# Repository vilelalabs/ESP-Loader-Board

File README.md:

Project created and updated live at  [Twitch.Tv/HenriqueVilelaMusic](https://twitch.tv/henriquevilelamusic)

# ESP-Loader-Board
CAD project of a board to upload programs to the ESP 8266 family boards

## Notes
- :warning: **The Source (fonte) may be a 3.3V DC !!!**
- **J1** and **J2** may be connected through a jumper on top side of the board. 
- **J3** and **J4** may be connected through a jumper on top side of the board. 
- The **JP1** jumper is used to enable/disable the **ESP8266 "upload mode"** where, connect to the GND, is the Upload Mode.

## Tested Boards
- ESP8266-01
- ESP8266-12S
- ESP8266-12E ( add: connect GPIO15 TO ground through a 300~10k resistor).

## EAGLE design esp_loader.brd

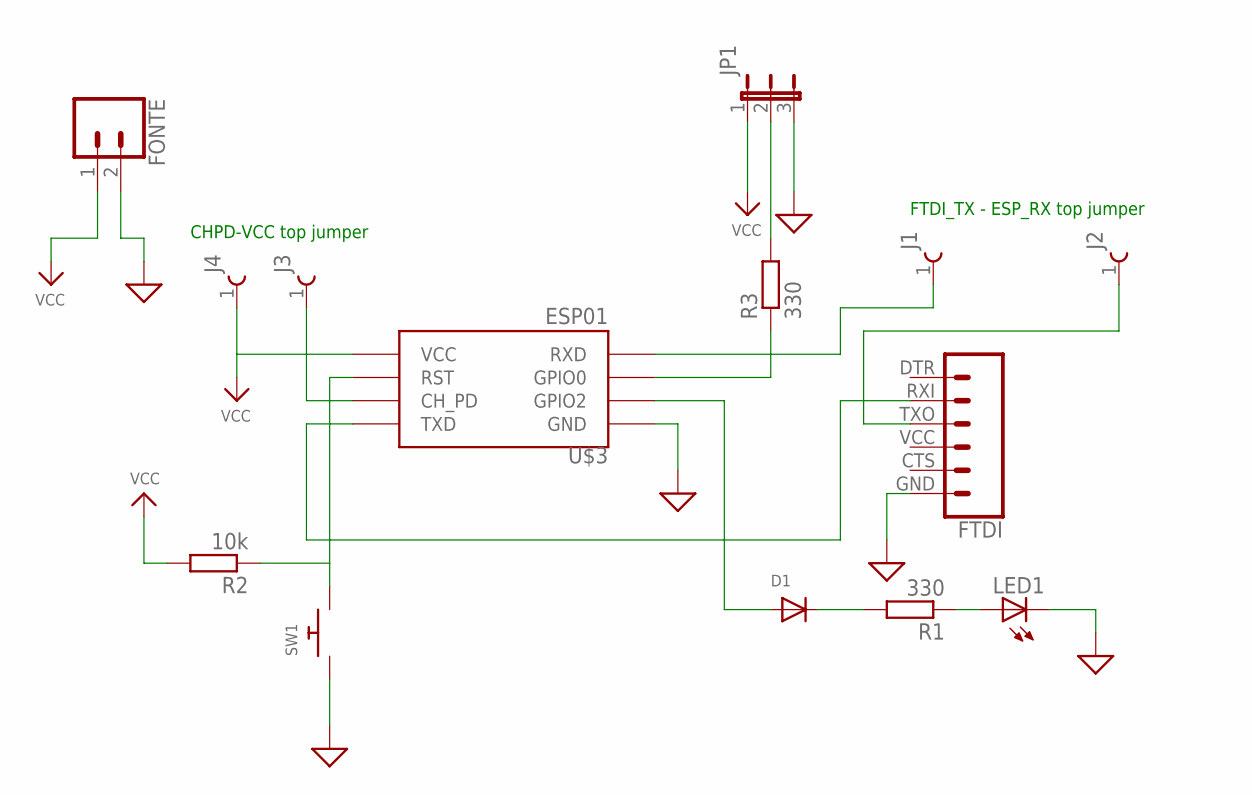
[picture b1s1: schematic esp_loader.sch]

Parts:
D1: DIODEDO-1N4148; DO-1N4148
FONTE: CONN_02POLAR; MOLEX-1X2
FTDI: 6_PIN_SERIAL_CABLEPTH; FTDI_BASIC
J1, J2, J3, J4: 61300111121
JP1: JP2E; JP2
LED1: LED5MM
R1, R3: 330; 0411/15
R2: 10k; 0411/15
SW1: SWITCH_PUSHBUTTONEVQ-PE; TACT_PANA-EVQ
U$3: ESP01

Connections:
GND: FONTE.2, FTDI.GND (6), JP1.3, LED1.K (C), SW1.P$1, U$3.GND
unnamed: R3.1, U$3.GPIO0
unnamed: JP1.2, R3.2
unnamed: FTDI.TXO (3), J2.1
unnamed: FTDI.RXI (2), U$3.TX (TXD)
unnamed: D1.A, U$3.GPIO2
unnamed: D1.C, R1.2
unnamed: LED1.A, R1.1
unnamed: R2.1, SW1.P$2, U$3.RST
unnamed: J3.1, U$3.CH_PD
unnamed: J1.1, U$3.RX (RXD)
VCC: FONTE.1, J4.1, JP1.1, R2.2, U$3.VCC

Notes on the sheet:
CHPD-VCC top jumper
FTDI_TX - ESP_RX top jumper

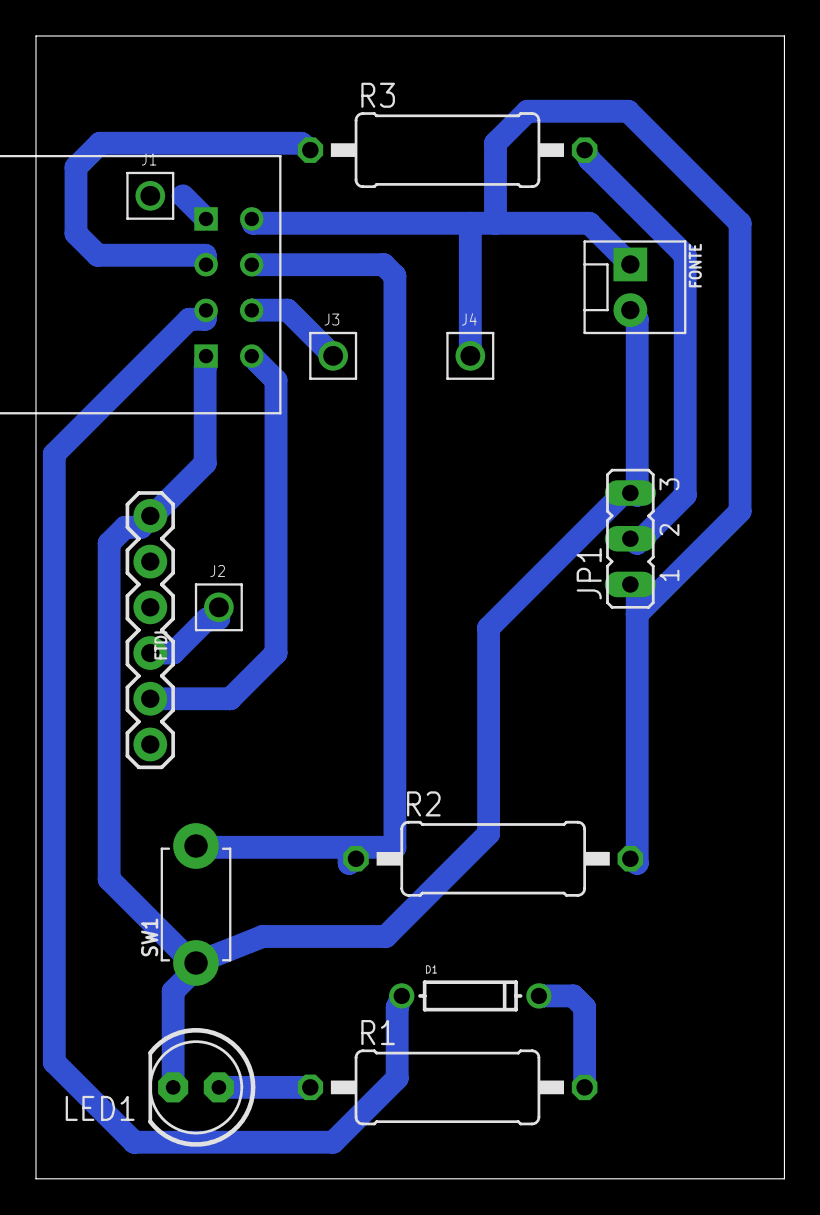
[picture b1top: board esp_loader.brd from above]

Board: 2 copper layers, 41.6 x 63.5 mm, 14 parts (0 on the bottom side), 12 nets.

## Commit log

2021-02-20 Add JPEG files for Schematic and Board

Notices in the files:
parts and their libraries:
SparkFun-Connectors: Licensing: Creative Commons ShareAlike 4.0 International - https://creativecommons.org/licenses/by-sa/4.0
Wurth_Elektronik_Electromechanic_Board_t: Copyright: Würth Elektronik
